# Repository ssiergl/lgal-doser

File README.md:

<!-- SPDX-FileCopyrightText: 2026 Lars Greiss / LG Aquatic Life -->
<!-- SPDX-License-Identifier: GPL-3.0-or-later -->

<p align="center"></p>

#  LGAL Doser

*English · [Deutsch](README.de.md)*

Open dosing pump for reef aquariums by **LG Aquatic Life**. The first device has five
peristaltic pumps with stepper motors, controlled by an ESP32-S3; versions with fewer pumps
are planned. It is operated through a web UI in the browser and, if you like, from Home
Assistant as well. Firmware, circuit board and enclosure are open in this repository.

<h3 align="center">Dashboard – Desktop</h3>
<p align="center">
  <picture>
    <source media="(prefers-color-scheme: dark)" srcset="docs/images/en/overview-dark.png">
    
  </picture>
</p>

<h3 align="center">Dashboard – Mobile</h3>

<h3 align="center">A few highlights</h3>

> **Important:** A dosing pump adds substances to the aquarium that can kill animals in the
> wrong amount. Read the [safety notes](#safety-and-liability) before first use.

## Features

- **Five independent pumps:** Kamoer KPHM100-ST with TMC2209 drivers. The pumps run quietly in
  StealthChop mode with a soft ramp, and all of them can run at the same time.
- **Accurate dosing:** calibration wizard with a measuring cup, retract against dripping, tube
  priming by holding a button in the wizard (stops at once on release or when the connection
  drops).
- **Schedules:** per pump a daily amount spread over N doses, or fixed times with their own
  amount; daily, on weekdays or every N days. Plus boost (extra amount over a few days) and
  lock times between pumps, e.g. no calcium right after alkalinity.
- **Protection against overdosing:** hard daily limit per pump, container level with range in
  days, all schedules checked on save, defined behaviour after a power cut.
- **Web UI** right on the device, no cloud and no app: overview of all pumps, history with
  charts, **simple** and **pro** view, dark and light theme, in English, German, French,
  Spanish, Italian, Dutch, Polish, Turkish and Chinese (all but English and German
  machine-translated).
- **Networked:** LAN as the main connection, Wi-Fi as fallback. Setup Wi-Fi with a setup
  wizard, time via NTP with a clock module as fallback.
- **Home Assistant / MQTT:** automatic discovery, sensors per pump, optional dosing and
  switching from Home Assistant, update entity. TLS with your own CA certificate.
- **Updates over the network** with automatic rollback if a new firmware does not start
  cleanly. Optionally the device checks for new versions daily.
- **Status LED** (red, yellow, green …) with night mode, one button for setup and factory reset.

## Hardware at a glance

| Assembly | Part |
|---|---|
| Controller | Waveshare ESP32-S3-DEV-KIT-N16R8 (firmware also for N8R8 and N32R8) |
| Pumps | 5× Kamoer KPHM100-ST, 24 V, tube BPT 3×5 mm |
| Motor drivers | 5× TMC2209 (StepStick), configured over UART |
| Network | USR-ES1 (W5500) for LAN, Wi-Fi in the ESP32-S3 |
| Clock | DS3231 with backup battery |
| Controls | RGB status light, button |
| Supply | 24 V external, power supply with at least 2.5 A (60 W) |

Pin assignment and circuit: [CLAUDE.md](CLAUDE.md).

## Documentation

| Document | For |
|---|---|
| [User guide](docs/user-guide.md) | owners: setup, calibrating pumps, schedules, daily use, troubleshooting |
| [Build guide](docs/build-guide.md) | makers: parts list, electrical safety, flashing the firmware, assembly and test |
| [Technical documentation](docs/technical.md) | developers: building the firmware, first USB flash, API, MQTT, internals |
| [Changelog](CHANGELOG.md) | what changed from version to version |
| [Security](SECURITY.md) | security model, known limits, reporting vulnerabilities privately |

German versions of the README and the guides are in [README.de.md](README.de.md) and
[docs/de/](docs/de/).

## Project status

The firmware is complete (milestones M0–M6) and tested with host tests, fuzzers and a device
mock. Circuit board v1.0 (11/2026) is built, v1.1 is designed.

You can try the web UI in the browser without a device:

```bash
python3 tools/mock/webui_server.py
```

Then open `http://localhost:8767/`, password `test-admin-pw`. More in the
[technical documentation](docs/technical.md#mock-server-without-a-device).

## Repository

```
components/   firmware (ESP-IDF components) and web UI
main/         firmware start-up
tools/        provisioning, update upload, release build, device mock
tests/        host tests and fuzzers
docs/         documentation, German versions in docs/de/
hardware/     enclosure (STL …) and circuit board (schematic, Gerber …), one folder per version
```

## Reporting bugs

Please open an issue with the "Bug report" template, in English or German. Include the firmware
version and, if possible, the log from the maintenance page – without passwords or keys.
Security vulnerabilities must not be reported publicly; see [SECURITY.md](SECURITY.md).

## Safety and liability

**Dosing errors can kill animals.** A wrong amount, a forgotten calibration, swapped tubes, a
software bug or a defect can put too much or too little of a substance into the tank within a
short time. Therefore:

- Keep containers no larger than needed: what is not in the container cannot reach the tank.
- Set a **daily limit** for every pump that safely rules out a dangerous amount.
- After every change (tube, container, schedule, firmware update) calibrate or check, and test
  the water more often in the following days.
- Route the tube ends so that nothing keeps flowing when the pump stands still (check valve or
  tube end above the water level).

The device runs on 24 V from an external power supply. Use only a certified power supply with
safety extra-low voltage (SELV), protect the electronics from splash and salt water, and plug
the power supply into a socket protected by a residual current device (RCD).

This project is provided without any warranty (see the licenses). Building and operating it is
at your own risk; the authors are not liable for damage to animals, aquarium, furnishings or
other property.

## License

- Firmware and software: **GPL-3.0-or-later**, see [LICENSE](LICENSE) and
  [THIRD-PARTY-NOTICES.txt](THIRD-PARTY-NOTICES.txt).
- Hardware (enclosure, schematic, circuit board, Gerber): **CC BY-NC-SA 4.0**, see
  [LICENSE-hardware.md](LICENSE-hardware.md). Commercial use only with written permission.
- Name and logo of LG Aquatic Life: not covered by these licenses, see
  [TRADEMARKS.md](TRADEMARKS.md).

Each source and documentation file names its copyright holder and license in an SPDX header
at the top. Files that cannot hold a comment (KiCad, Gerber, STL, PDF, JSON) follow the list
above.

Copyright © 2026 Lars Greiss / LG Aquatic Life

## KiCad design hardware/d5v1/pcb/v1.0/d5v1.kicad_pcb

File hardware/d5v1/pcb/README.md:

<!-- SPDX-FileCopyrightText: 2026 Lars Greiss / LG Aquatic Life -->
<!-- SPDX-License-Identifier: CC-BY-NC-SA-4.0 -->

# d5v1 – circuit board

Circuit boards of the LGAL Doser 5 (board ID `d5v1`). All versions share the same ESP32-S3 pin
assignment and run the same firmware build.

| Version | Folder | Status |
|---|---|---|
| v1.0 (11/2026) | [`v1.0/`](v1.0/) | built; needs two rework wires, see [below](#rework-rx-lines-of-the-driver-uart) |
| v1.1 | [`v1.1/`](v1.1/) | [Gerber and drill files](v1.1/gerber/), see the [revision plan](v1.1/plan.md) |

Each version folder holds:

| File | Purpose |
|---|---|
| `d5v1.kicad_pro`, `d5v1.kicad_sch`, `d5v1.kicad_pcb` | KiCad 10 project: schematic and layout for editing |
| `lgal_doser.kicad_sym`, `lgal_doser.pretty/` | project symbol and footprint library (ESP32-S3 socket, TMC2209 StepStick socket, Multimec 3F button), registered with project-relative paths in `sym-lib-table` and `fp-lib-table` |
| `bom.csv` | bill of materials: all parts with reference, value, footprint and example part number |
| `d5v1-schematic.pdf` | schematic for reading without KiCad |
| `gerber/` | Gerber and drill files for the board maker |

**Status v1.0:** the KiCad project (4 layers), the [bill of materials](v1.0/bom.csv), the
[schematic PDF](v1.0/d5v1-schematic.pdf) and the [Gerber and drill files](v1.0/gerber/) are
published (renamed from the old project name to `d5v1-*`; the drawing matches the layout in
`v1.0/`, plotted with "subtract soldermask from silkscreen"). Manufacturing options for both
versions: 4 layers, 1.6 mm, no specified stackup, 1 oz outer and 0.5 oz inner copper, HASL. The quantities in `bom.csv` are for one device; plug-in modules, pumps, power
supply and other device parts are listed in the [build guide](../../../docs/build-guide.md#1-parts-list).

The ESP32-S3 pin assignment and the circuit (UART addresses of the drivers, pull-ups, LED
drivers, strapping pins) are fixed and described in [CLAUDE.md](../../../CLAUDE.md); the firmware
follows them.

## Rework: RX lines of the driver UART

Board v1.0 connects each driver bus to only one GPIO (38, 39) through its 1 kΩ series resistor
(R3, R4). On such a single-wire bus the pull-downs on PDN_UART of the driver modules pull the line
LOW while the ESP listens, which makes the replies of the drivers unreliable. The firmware
therefore uses the two-pin standard circuit: TX keeps the GPIO and the 1 kΩ, RX is a second GPIO
directly on the bus. On board v1.0 two wires are added for this:

| Bus | Pumps | TX (on the board, through 1 kΩ) | RX (wire, directly on the bus) |
|---|---|---|---|
| A | 1–4 | GPIO 38 | GPIO 4 |
| B | 5 | GPIO 39 | GPIO 5 |

Solder each wire, without power, from the GPIO pin of the ESP socket header to the driver side
of the series resistor of its bus, i.e. to the PDN_UART line of the drivers. Without these wires
the firmware gets no replies from the drivers and the pumps do not run. Board v1.1 routes the RX
lines on the board. The board ID stays `d5v1`.

License: CC BY-NC-SA 4.0, see [LICENSE-hardware.md](../../../LICENSE-hardware.md).

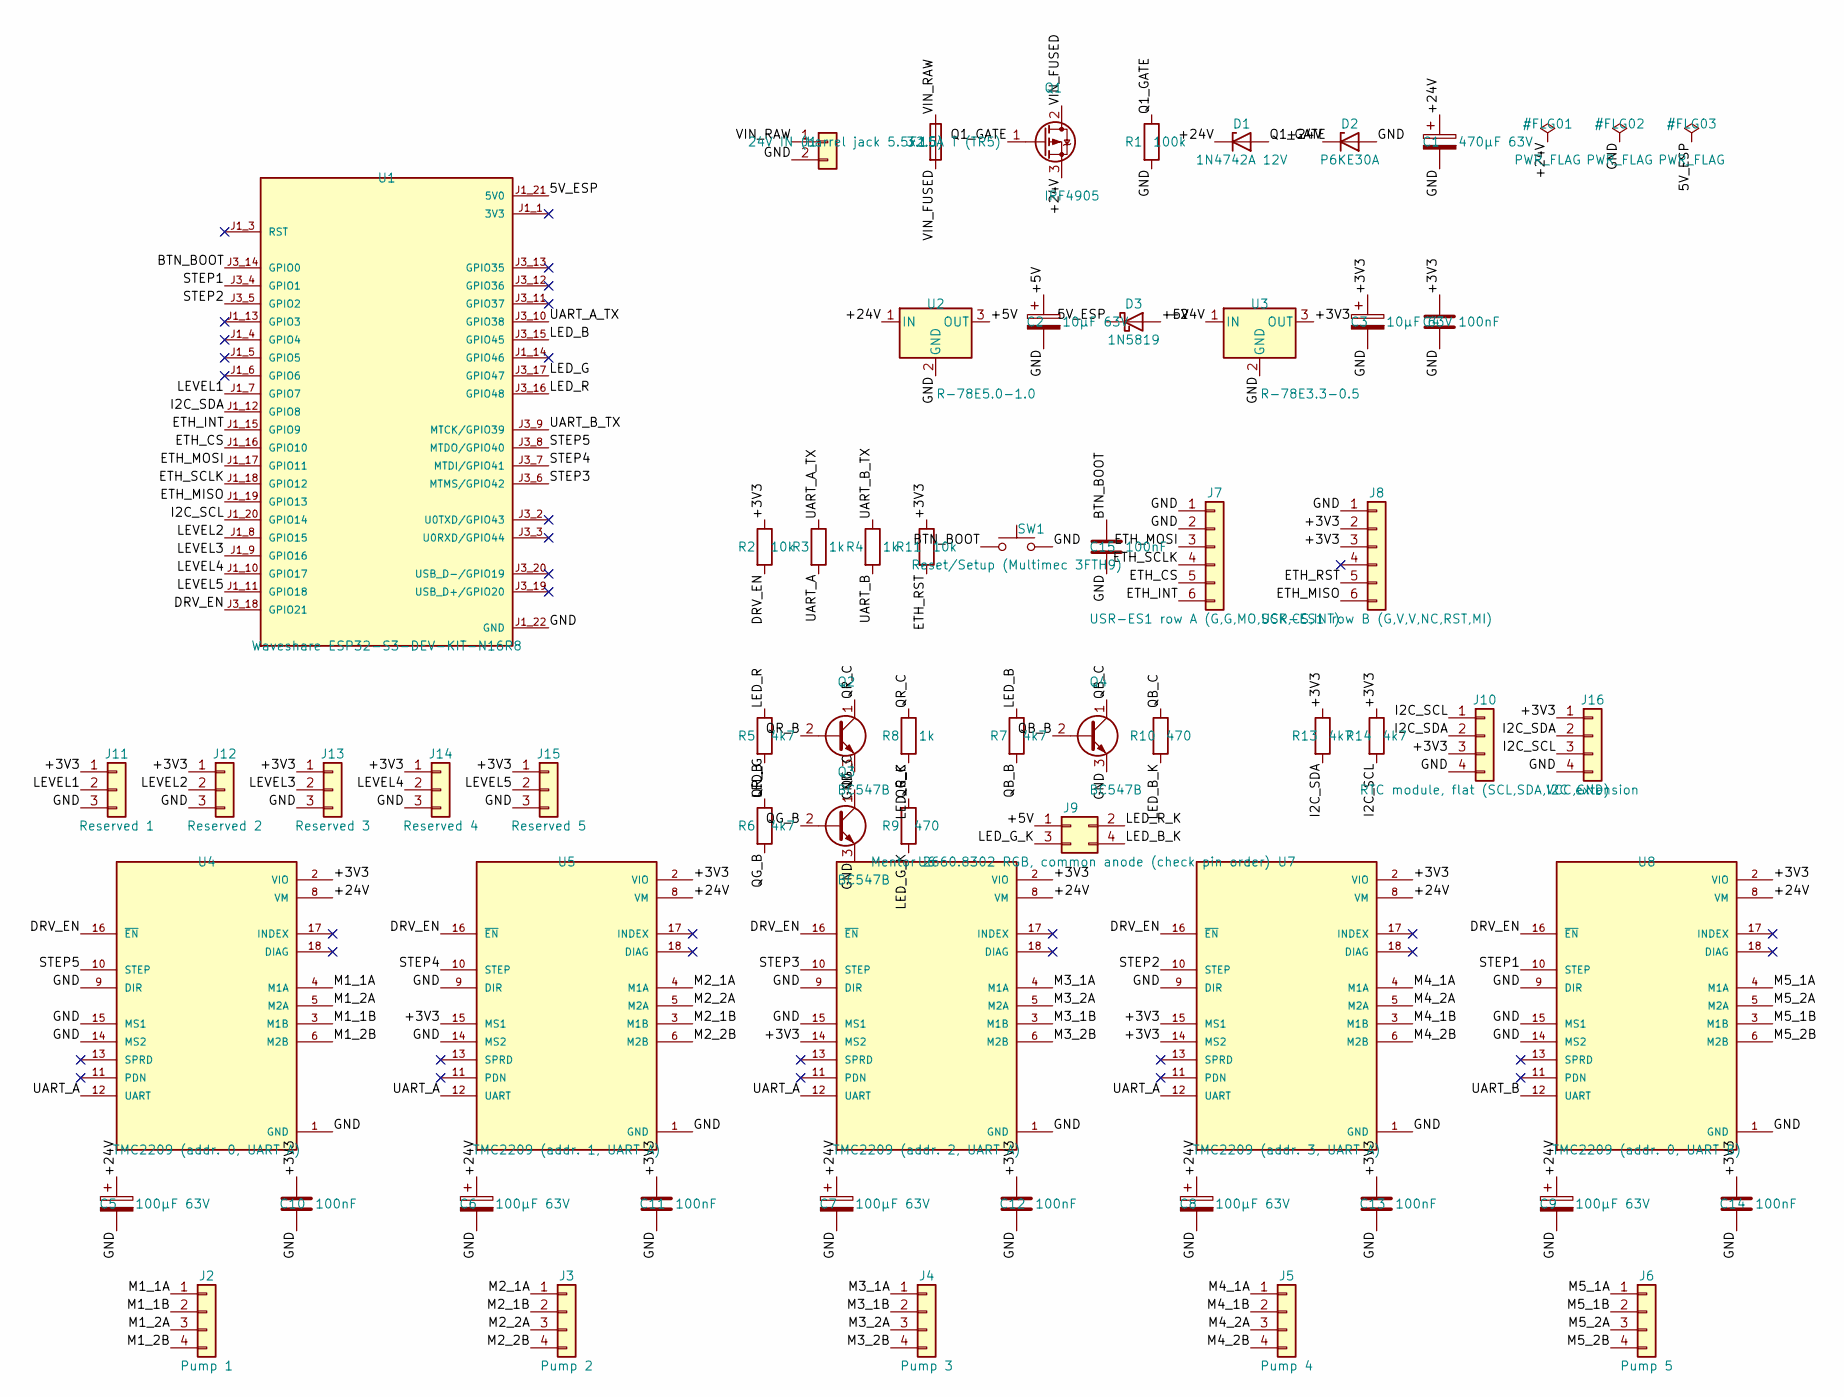
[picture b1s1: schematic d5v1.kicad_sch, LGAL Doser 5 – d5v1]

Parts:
C1: 470µF 63V; CP_Radial_D12.5mm_P5.00mm
C2, C3: 10µF 63V; CP_Radial_D5.0mm_P2.00mm
C4, C10, C11, C12, C13, C14, C15: 100nF; C_Disc_D5.0mm_W2.5mm_P5.00mm
C5, C6, C7, C8, C9: 100µF 63V; CP_Radial_D10.0mm_P5.00mm
D1: 1N4742A 12V; D_DO-41_SOD81_P10.16mm_Horizontal
D2: P6KE30A; D_DO-15_P10.16mm_Horizontal
D3: 1N5819; D_DO-41_SOD81_P10.16mm_Horizontal
F1: 3.15A T (TR5); Fuseholder_TR5_Littelfuse_No560_No460
J1: 24V IN (barrel jack 5.5x2.5); BarrelJack_Horizontal
J2: Pump 1; JST_XH_B4B-XH-A_1x04_P2.50mm_Vertical
J3: Pump 2; JST_XH_B4B-XH-A_1x04_P2.50mm_Vertical
J4: Pump 3; JST_XH_B4B-XH-A_1x04_P2.50mm_Vertical
J5: Pump 4; JST_XH_B4B-XH-A_1x04_P2.50mm_Vertical
J6: Pump 5; JST_XH_B4B-XH-A_1x04_P2.50mm_Vertical
J7: USR-ES1 row A (G,G,MO,SCK,CS,INT); PinSocket_1x06_P2.54mm_Vertical
J8: USR-ES1 row B (G,V,V,NC,RST,MI); PinSocket_1x06_P2.54mm_Vertical
J9: Mentor 2660.8302 RGB, common anode (check pin ord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; PinHeader_2x02_P2.54mm_Vertical
J10: RTC module, flat (SCL,SDA,VCC,GND); PinSocket_1x04_P2.54mm_Vertical
J11: Reserved 1; JST_XH_B3B-XH-A_1x03_P2.50mm_Vertical
J12: Reserved 2; JST_XH_B3B-XH-A_1x03_P2.50mm_Vertical
J13: Reserved 3; JST_XH_B3B-XH-A_1x03_P2.50mm_Vertical
J14: Reserved 4; JST_XH_B3B-XH-A_1x03_P2.50mm_Vertical
J15: Reserved 5; JST_XH_B3B-XH-A_1x03_P2.50mm_Vertical
J16: I2C extension; JST_XH_B4B-XH-A_1x04_P2.50mm_Vertical
Q1: IRF4905; TO-220-3_Vertical
Q2, Q3, Q4: BC547B; TO-92_Inline
R1: 100k; R_Axial_DIN0207_L6.3mm_D2.5mm_P7.62mm_Horizontal
R2, R11: 10k; R_Axial_DIN0207_L6.3mm_D2.5mm_P7.62mm_Horizontal
R3, R4, R8: 1k; R_Axial_DIN0207_L6.3mm_D2.5mm_P7.62mm_Horizontal
R5, R6, R7, R13, R14: 4k7; R_Axial_DIN0207_L6.3mm_D2.5mm_P7.62mm_Horizontal
R9, R10: 470; R_Axial_DIN0207_L6.3mm_D2.5mm_P7.62mm_Horizontal
SW1: Reset/Setup (Multimec 3FTH9); Multimec_3FTH9
U1: Waveshare ESP32-S3-DEV-KIT-N16R8; Waveshare_ESP32-S3-DEV-KIT_Socket
U2: R-78E5.0-1.0; Converter_DCDC_RECOM_R-78E-0.5_THT
U3: R-78E3.3-0.5; Converter_DCDC_RECOM_R-78E-0.5_THT
U4: TMC2209 (addr. 0, UART A); TMC2209_StepStick_V2_Socket_NoDiag
U5: TMC2209 (addr. 1, UART A); TMC2209_StepStick_V2_Socket_NoDiag
U6: TMC2209 (addr. 2, UART A); TMC2209_StepStick_V2_Socket_NoDiag
U7: TMC2209 (addr. 3, UART A); TMC2209_StepStick_V2_Socket_NoDiag
U8: TMC2209 (addr. 0, UART B); TMC2209_StepStick_V2_Socket_NoDiag

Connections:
5V_ESP: D3.1 (K), U1.J1_21 (5V0)
+3V3: C3.1, C4.1, C10.1, C11.1, C12.1, C13.1, C14.1, J8.2, J8.3, J10.3, J11.1, J12.1, J13.1, J14.1, J15.1, J16.1, R2.1, R11.1, R13.1, R14.1, U3.3 (OUT), U4.2 (VIO), U5.2 (VIO), U5.15 (MS1), U6.2 (VIO), U6.14 (MS2), U7.2 (VIO), U7.14 (MS2), U7.15 (MS1), U8.2 (VIO)
+5V: C2.1, D3.2 (A), J9.1, U2.3 (OUT)
+24V: C1.1, C5.1, C6.1, C7.1, C8.1, C9.1, D1.1 (K), D2.1 (K), Q1.3 (S), U2.1 (IN), U3.1 (IN), U4.8 (VM), U5.8 (VM), U6.8 (VM), U7.8 (VM), U8.8 (VM)
BTN_BOOT: C15.1, SW1.1, U1.J3_14 (GPIO0)
DRV_EN: R2.2, U1.J3_18 (GPIO21), U4.16 (~EN), U5.16 (~EN), U6.16 (~EN), U7.16 (~EN), U8.16 (~EN)
ETH_CS: J7.5, U1.J1_16 (GPIO10)
ETH_INT: J7.6, U1.J1_15 (GPIO9)
ETH_MISO: J8.6, U1.J1_19 (GPIO13)
ETH_MOSI: J7.3, U1.J1_17 (GPIO11)
ETH_RST: J8.5, R11.2
ETH_SCLK: J7.4, U1.J1_18 (GPIO12)
GND: C1.2, C2.2, C3.2, C4.2, C5.2, C6.2, C7.2, C8.2, C9.2, C10.2, C11.2, C12.2, C13.2, C14.2, C15.2, D2.2 (A), J1.2, J7.1, J7.2, J8.1, J10.4, J11.3, J12.3, J13.3, J14.3, J15.3, J16.4, Q2.3 (E), Q3.3 (E), Q4.3 (E), R1.2, SW1.2, U1.J1_22 (GND), U1.J3_1 (GND), U1.J3_21 (GND), U1.J3_22 (GND), U2.2 (GND), U3.2 (GND), U4.1 (GND), U4.7 (GND), U4.9 (DIR), U4.14 (MS2), U4.15 (MS1), U5.1 (GND), U5.7 (GND), U5.9 (DIR), U5.14 (MS2), U6.1 (GND), U6.7 (GND), U6.9 (DIR), U6.15 (MS1), U7.1 (GND), U7.7 (GND), U7.9 (DIR), U8.1 (GND), U8.7 (GND), U8.9 (DIR), U8.14 (MS2), U8.15 (MS1)
I2C_SCL: J10.1, J16.3, R14.2, U1.J1_20 (GPIO14)
I2C_SDA: J10.2, J16.2, R13.2, U1.J1_12 (GPIO8)
LED_B: R7.1, U1.J3_15 (GPIO45)
LED_B_K: J9.4, R10.2
LED_G: R6.1, U1.J3_17 (GPIO47)
LED_G_K: J9.3, R9.2
LED_R: R5.1, U1.J3_16 (GPIO48)
LED_R_K: J9.2, R8.2
LEVEL1: J11.2, U1.J1_7 (GPIO7)
LEVEL2: J12.2, U1.J1_8 (GPIO15)
LEVEL3: J13.2, U1.J1_9 (GPIO16)
LEVEL4: J14.2, U1.J1_10 (GPIO17)
LEVEL5: J15.2, U1.J1_11 (GPIO18)
M1_1A: J2.1, U4.4 (M1A)
M1_1B: J2.2, U4.3 (M1B)
M1_2A: J2.3, U4.5 (M2A)
M1_2B: J2.4, U4.6 (M2B)
M2_1A: J3.1, U5.4 (M1A)
M2_1B: J3.2, U5.3 (M1B)
M2_2A: J3.3, U5.5 (M2A)
M2_2B: J3.4, U5.6 (M2B)
M3_1A: J4.1, U6.4 (M1A)
M3_1B: J4.2, U6.3 (M1B)
M3_2A: J4.3, U6.5 (M2A)
M3_2B: J4.4, U6.6 (M2B)
M4_1A: J5.1, U7.4 (M1A)
M4_1B: J5.2, U7.3 (M1B)
M4_2A: J5.3, U7.5 (M2A)
M4_2B: J5.4, U7.6 (M2B)
M5_1A: J6.1, U8.4 (M1A)
M5_1B: J6.2, U8.3 (M1B)
M5_2A: J6.3, U8.5 (M2A)
M5_2B: J6.4, U8.6 (M2B)
Q1_GATE: D1.2 (A), Q1.1 (G), R1.1
QB_B: Q4.2 (B), R7.2
QB_C: Q4.1 (C), R10.1
QG_B: Q3.2 (B), R6.2
QG_C: Q3.1 (C), R9.1
QR_B: Q2.2 (B), R5.2
QR_C: Q2.1 (C), R8.1
STEP1: U1.J3_4 (GPIO1), U8.10 (STEP)
STEP2: U1.J3_5 (GPIO2), U7.10 (STEP)
STEP3: U1.J3_6 (MTMS/GPIO42), U6.10 (STEP)
STEP4: U1.J3_7 (MTDI/GPIO41), U5.10 (STEP)
STEP5: U1.J3_8 (MTDO/GPIO40), U4.10 (STEP)
UART_A: R3.2, U4.12 (UART), U5.12 (UART), U6.12 (UART), U7.12 (UART)
UART_A_TX: R3.1, U1.J3_10 (GPIO38)
UART_B: R4.2, U8.12 (UART)
UART_B_TX: R4.1, U1.J3_9 (MTCK/GPIO39)
VIN_FUSED: F1.2, Q1.2 (D)
VIN_RAW: F1.1, J1.1

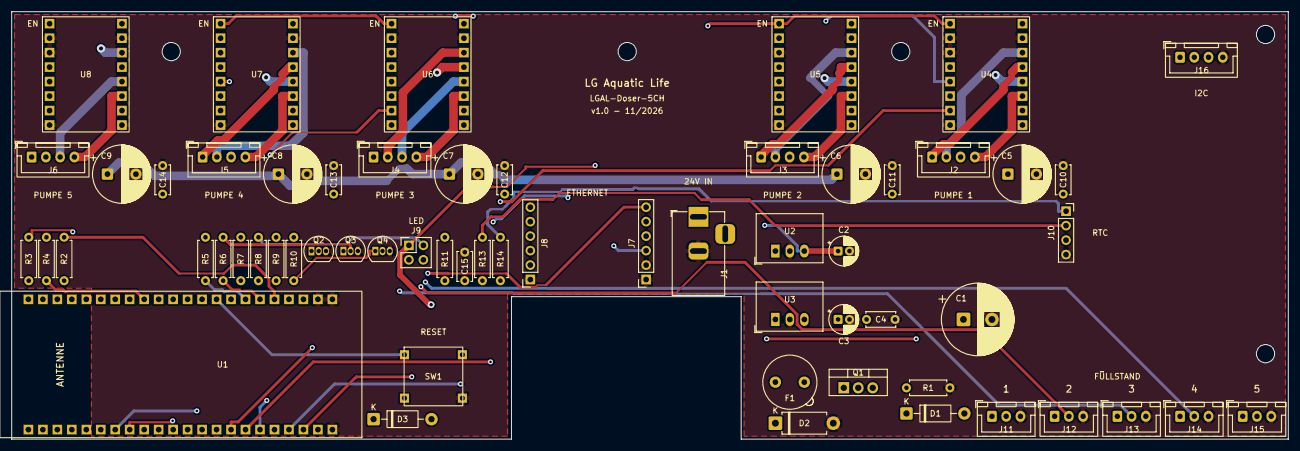
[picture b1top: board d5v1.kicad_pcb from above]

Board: 4 copper layers, 224.0 x 75.0 mm, 66 parts (0 on the bottom side), 64 nets.

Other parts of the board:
MH1, MH2, MH3, MH4, MH5: MountingHole_3.2mm

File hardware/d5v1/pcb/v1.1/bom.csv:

Item,Reference,Part,Qty,Value,Specification,Footprint (KiCad),Example part number,Note
1,"R1, R15",Resistor,2,100 kΩ,"metal film, 0.25 W, 1 %","R_Axial_DIN0207, 7.62 mm pitch",Yageo MFR-25FBF52-100K,"gate pull-down of the reverse-polarity protection Q1 (R1), 24 V sense divider (R15)"
2,"R2, R11, R16",Resistor,3,10 kΩ,"metal film, 0.25 W, 1 %","R_Axial_DIN0207, 7.62 mm pitch",Yageo MFR-25FBF52-10K,"pull-ups: driver enable (R2), Ethernet reset (R11); 24 V sense divider (R16)"
3,"R3, R4, R8",Resistor,3,1 kΩ,"metal film, 0.25 W, 1 %","R_Axial_DIN0207, 7.62 mm pitch",Yageo MFR-25FBF52-1K,"UART series resistors (R3, R4), LED red (R8)"
4,"R5, R6, R7, R13, R14",Resistor,5,4.7 kΩ,"metal film, 0.25 W, 1 %","R_Axial_DIN0207, 7.62 mm pitch",Yageo MFR-25FBF52-4K7,"LED base resistors (R5–R7), I²C pull-ups (R13, R14)"
5,"R9, R10",Resistor,2,470 Ω,"metal film, 0.25 W, 1 %","R_Axial_DIN0207, 7.62 mm pitch",Yageo MFR-25FBF52-470R,LED green/blue
6,C1,Electrolytic capacitor,1,470 µF / 63 V,"radial, low ESR, 105 °C, Ø 12.5 mm, at most 25 mm high",CP_Radial_D12.5mm_P5.00mm,Panasonic FR series 470 µF / 63 V,24 V input; mind the polarity
7,"C5, C6, C7, C8, C9",Electrolytic capacitor,5,100 µF / 63 V,"radial, low ESR, 105 °C, Ø 10 mm",CP_Radial_D10.0mm_P5.00mm,Panasonic FR series 100 µF / 63 V,one per driver at VM; mind the polarity
8,"C2, C3",Electrolytic capacitor,2,10 µF / 63 V,"radial, 105 °C, Ø 5 mm, 2 mm pitch",CP_Radial_D5.0mm_P2.00mm,Panasonic FR series 10 µF / 63 V,outputs of the 5 V and 3.3 V regulators; mind the polarity; not the 350 V types (too large)
9,"C4, C10–C16",Ceramic capacitor,8,100 nF,"50 V, X7R, 5 mm pitch",C_Disc_D5.0mm_W2.5mm_P5.00mm,Vishay K104K15X7RF5TL2,"decoupling 3.3 V (C4, C10–C14), button debounce (C15), 24 V sense filter (C16)"
10,D1,Zener diode,1,12 V / 1 W,glass or plastic,D_DO-41_SOD81_P10.16mm,1N4742A,gate protection of Q1; mind the cathode
11,D2,TVS diode,1,"30 V, 600 W",unidirectional,D_DO-15_P10.16mm,P6KE30A,overvoltage protection 24 V; mind the cathode
12,D3,Schottky diode,1,40 V / 1 A,,D_DO-41_SOD81_P10.16mm,1N5819,5 V to the ESP32; mind the cathode
13,Q1,P-channel MOSFET,1,IRF4905,"−55 V, −74 A","TO-220-3, vertical",Infineon IRF4905PBF,reverse-polarity protection
14,"Q2, Q3, Q4",NPN transistor,3,BC547B,"45 V, 100 mA",TO-92 inline,BC547B,LED drivers red/green/blue
15,U2,DC/DC regulator,1,5 V / 1 A,input up to 28 V,SIP-3,RECOM R-78E5.0-1.0,supply of the ESP32 board
16,U3,DC/DC regulator,1,3.3 V / 0.5 A,input up to 28 V,SIP-3,RECOM R-78E3.3-0.5,logic supply
17,F1,Fuse holder,1,TR5,5.08 mm pitch,Fuseholder_TR5_Littelfuse_No560_No460,Littelfuse 560 series (or compatible),
18,F1,Fuse,1,3.15 A slow-blow (T),TR5,–,Littelfuse 372 series 3.15 A T,replace only with the same value
19,J1,DC barrel jack,1,5.5 × 2.5 mm,"PCB mount, horizontal, centre positive",BarrelJack_Horizontal,any 5.5 × 2.5 mm PCB barrel jack,points down into the niche of the enclosure; check the pin layout against the footprint before soldering
20,"J2–J6, J10, J16",JST-XH header,7,4-pin,"2.5 mm pitch, vertical",JST_XH_B4B-XH-A_1x04_P2.50mm_Vertical,JST B4B-XH-A(LF)(SN),"pumps 1–5 (J2–J6), RTC cable (J10), I²C extension (J16)"
21,"J7, J8",Socket strip,2,1 × 6,2.54 mm pitch,PinSocket_1x06_P2.54mm_Vertical,"socket strip 1 × 6, 2.54 mm",Ethernet module USR-ES1 (RJ45 points down into the niche)
22,J9,Pin header,1,2 × 2,"2.54 mm pitch, straight",PinHeader_2x02_P2.54mm_Vertical,"pin header 2 × 2, 2.54 mm",connection of the Mentor RGB light
23,SW1,Push button,1,Multimec 3FTH9,PCB button without cap,Multimec_3FTH9 (project library),Mec 3FTH9,operated with a paper clip through the back wall
24,U1 (socket),Socket strip,4,1 × 8,"2.54 mm pitch, 7 mm high",–,"socket strip 1 × 8, 7 mm",ESP32 board: per row 1 × 8 + 1 × 8 + 1 × 6 = 22 pins
25,U1 (socket),Socket strip,2,1 × 6,"2.54 mm pitch, 7 mm high",–,"socket strip 1 × 6, 7 mm","ESP32 board, see above"
26,U4–U8 (socket),Socket strip,10,1 × 8,"2.54 mm pitch, 7 mm high",–,"socket strip 1 × 8, 7 mm",2 per driver

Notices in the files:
README.md:
License: GPL-3.0 | CC BY-NC-SA 4.0
